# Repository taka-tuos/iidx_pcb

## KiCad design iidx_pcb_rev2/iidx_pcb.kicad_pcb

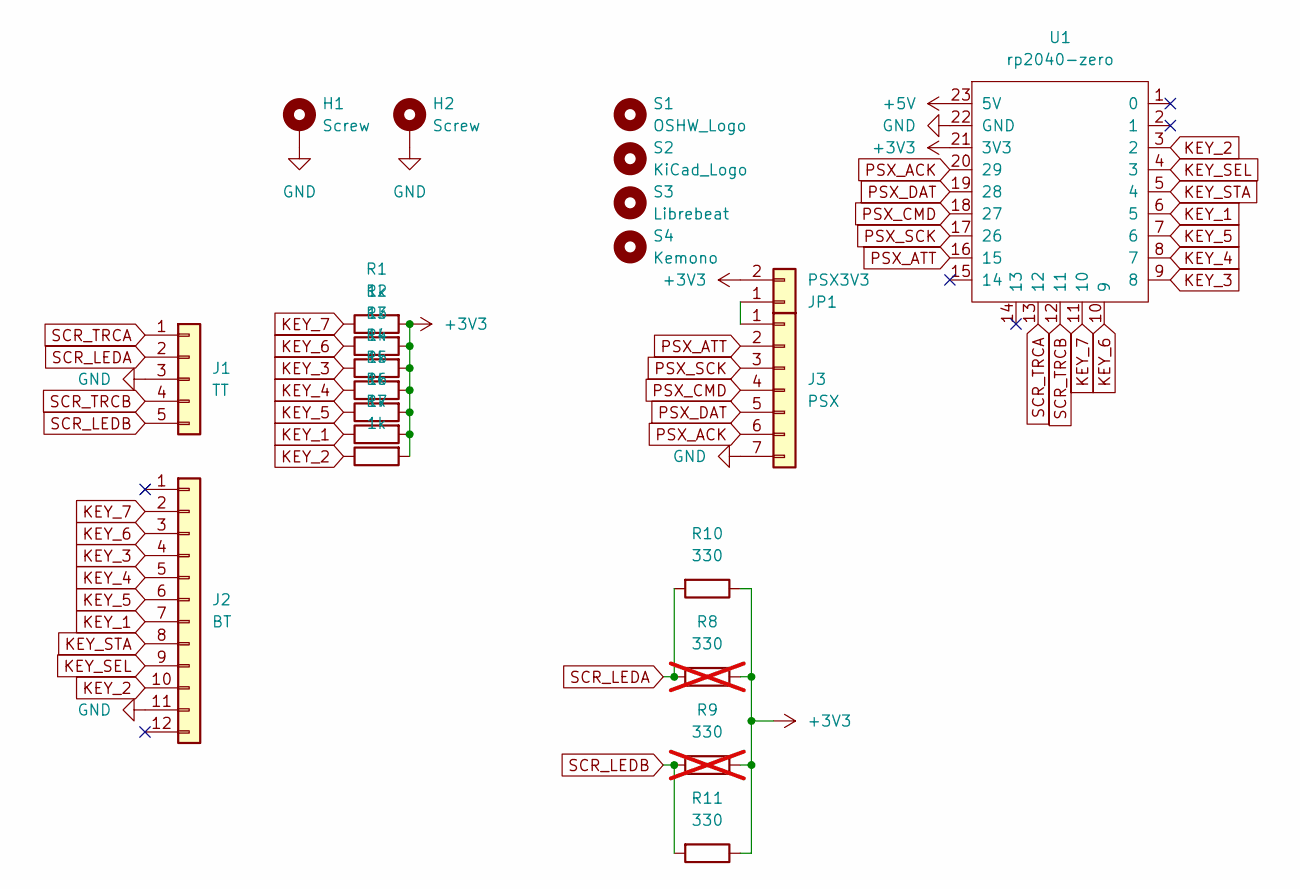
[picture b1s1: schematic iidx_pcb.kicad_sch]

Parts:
H1, H2: Screw; MountingHole_3.2mm_M3_DIN965_Pad
J1: TT; PinSocket_1x05_P2.00mm_Vertical
J2: BT; PinSocket_1x12_P2.00mm_Vertical
J3: PSX; PinSocket_1x07_P2.54mm_Vertical
JP1: PSX3V3; PinHeader_1x02_P2.54mm_Vertical
R1, R2, R3, R4, R5, R6, R7: 1k; R_Axial_DIN0204_L3.6mm_D1.6mm_P5.08mm_Horizontal
R8, R9: 330; R_Axial_DIN0204_L3.6mm_D1.6mm_P5.08mm_Horizontal; not fitted
R10, R11: 330; R_0805_2012Metric_Pad1.20x1.40mm_HandSolder
S1: OSHW_Logo; OSHW-Logo2_9.8x8mm_SilkScreen
S2: KiCad_Logo; KiCad-Logo2_6mm_SilkScreen
S3: Librebeat; Project_Librebeat_Logo
S4: Kemono; Kemono_Symbol
U1: rp2040-zero; rp2040-zero-tht

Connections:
+3V3: JP1.2, R1.2, R2.2, R3.2, R4.2, R5.2, R6.2, R7.2, R8.1, R9.1, R10.1, R11.1, U1.21 (3V3)
+5V: U1.23 (5V)
GND: H1.1, H2.1, J1.3, J2.11, J3.7, U1.22 (GND)
KEY_1: J2.7, R6.1, U1.6 (5)
KEY_2: J2.10, R7.1, U1.3 (2)
KEY_3: J2.4, R3.1, U1.9 (8)
KEY_4: J2.5, R4.1, U1.8 (7)
KEY_5: J2.6, R5.1, U1.7 (6)
KEY_6: J2.3, R2.1, U1.10 (9)
KEY_7: J2.2, R1.1, U1.11 (10)
KEY_SEL: J2.9, U1.4 (3)
KEY_STA: J2.8, U1.5 (4)
unnamed: J3.1, JP1.1
PSX_ACK: J3.6, U1.20 (29)
PSX_ATT: J3.2, U1.16 (15)
PSX_CMD: J3.4, U1.18 (27)
PSX_DAT: J3.5, U1.19 (28)
PSX_SCK: J3.3, U1.17 (26)
SCR_LEDA: J1.2, R8.2, R10.2
SCR_LEDB: J1.5, R9.2, R11.2
SCR_TRCA: J1.1, U1.13 (12)
SCR_TRCB: J1.4, U1.12 (11)

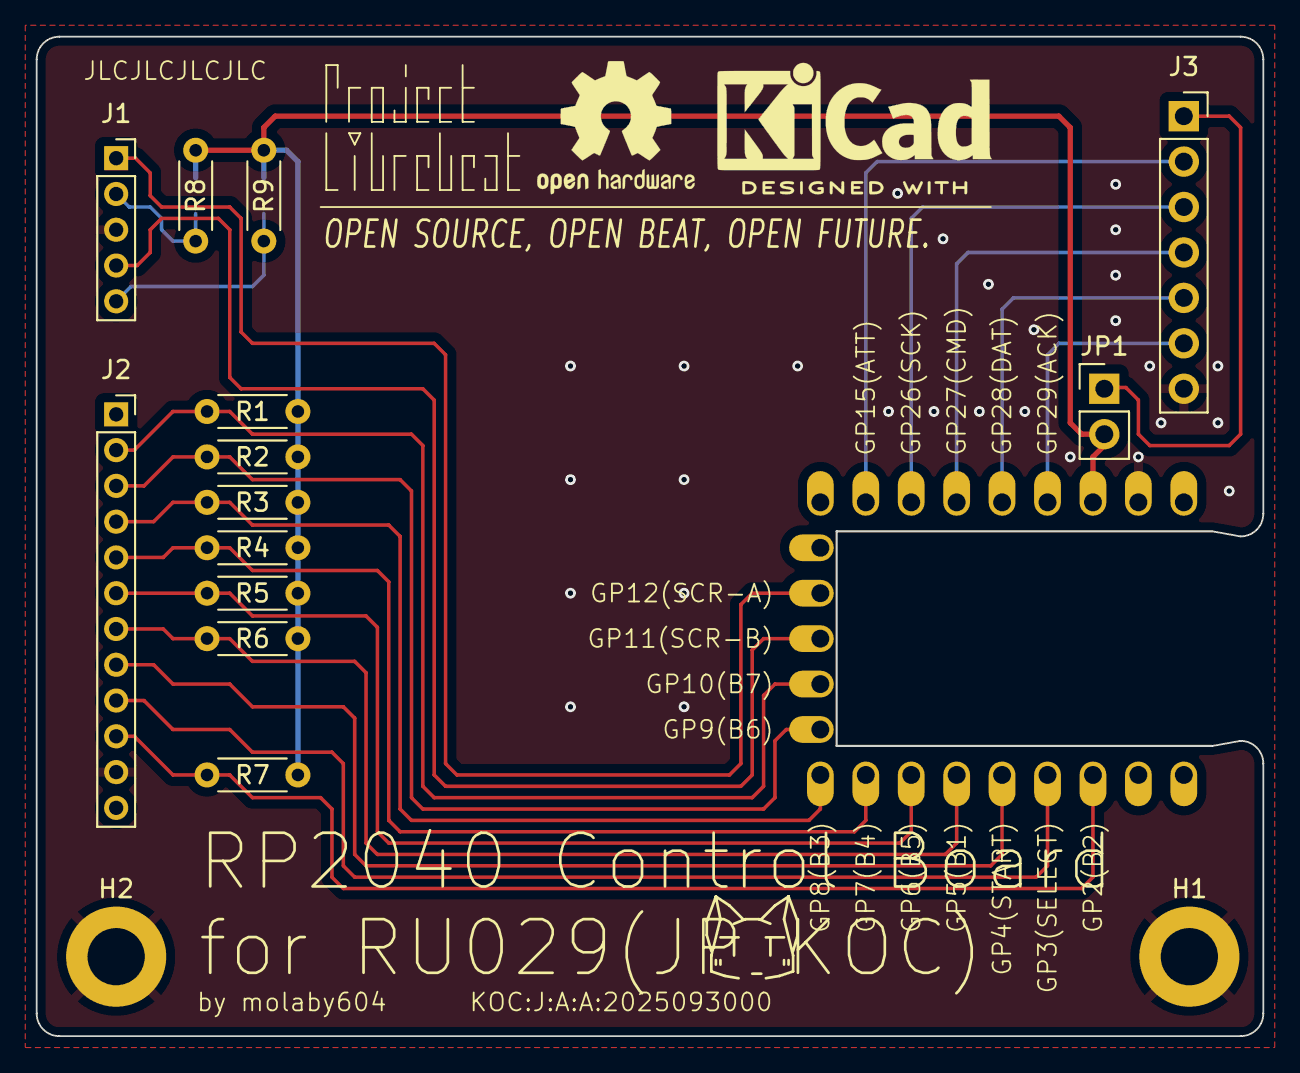
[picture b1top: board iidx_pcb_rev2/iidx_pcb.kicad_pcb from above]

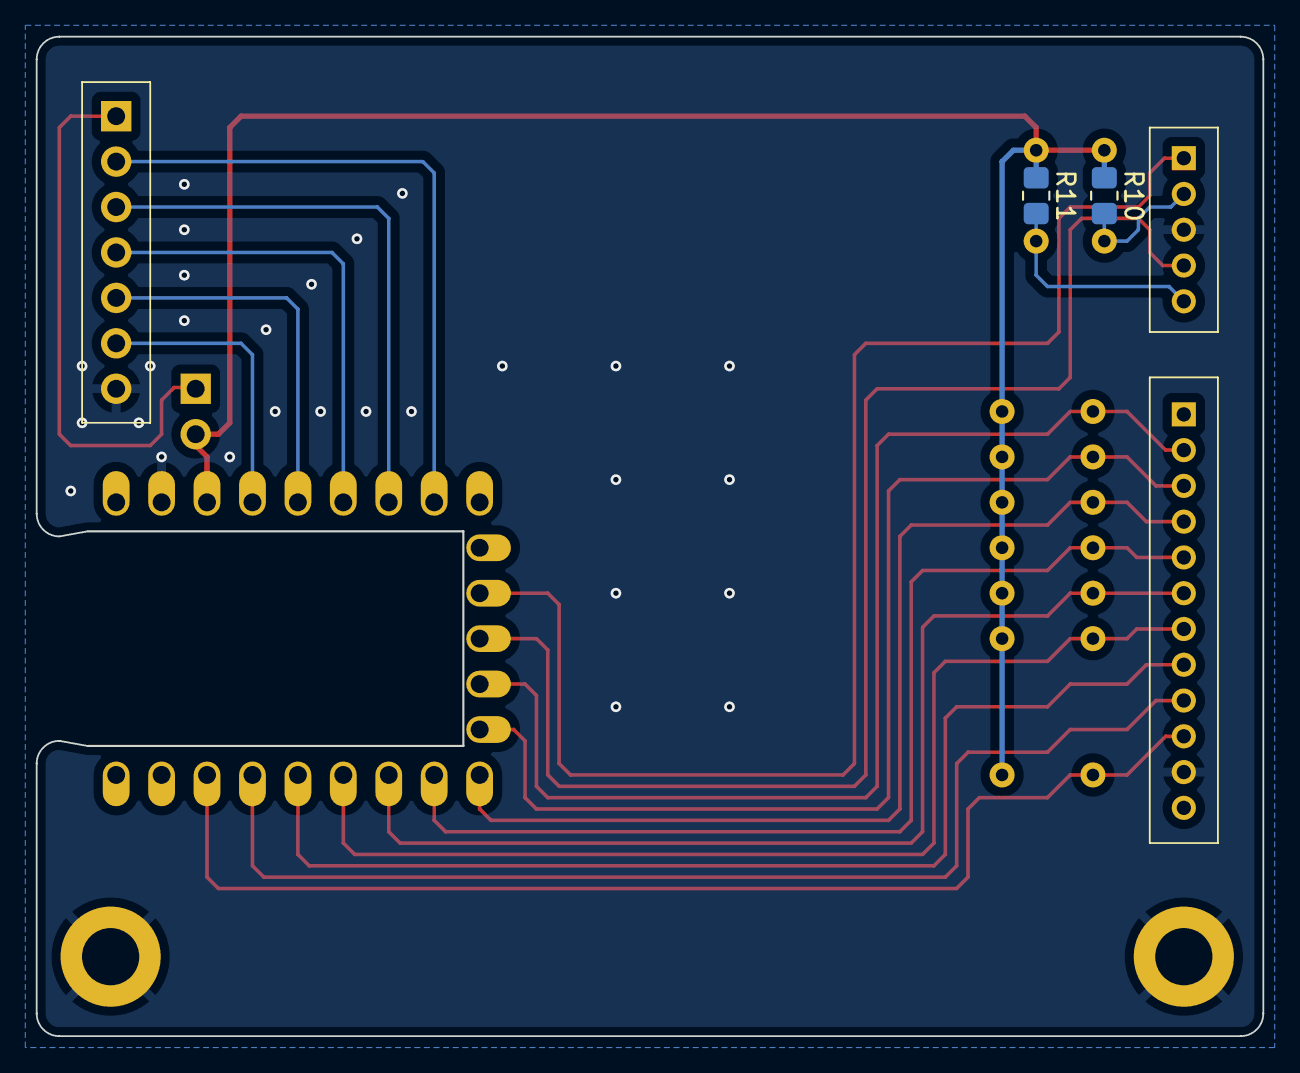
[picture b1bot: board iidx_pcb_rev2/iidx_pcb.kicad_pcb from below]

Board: 2 copper layers, 68.6 x 55.9 mm, 22 parts (2 on the bottom side), 21 nets.

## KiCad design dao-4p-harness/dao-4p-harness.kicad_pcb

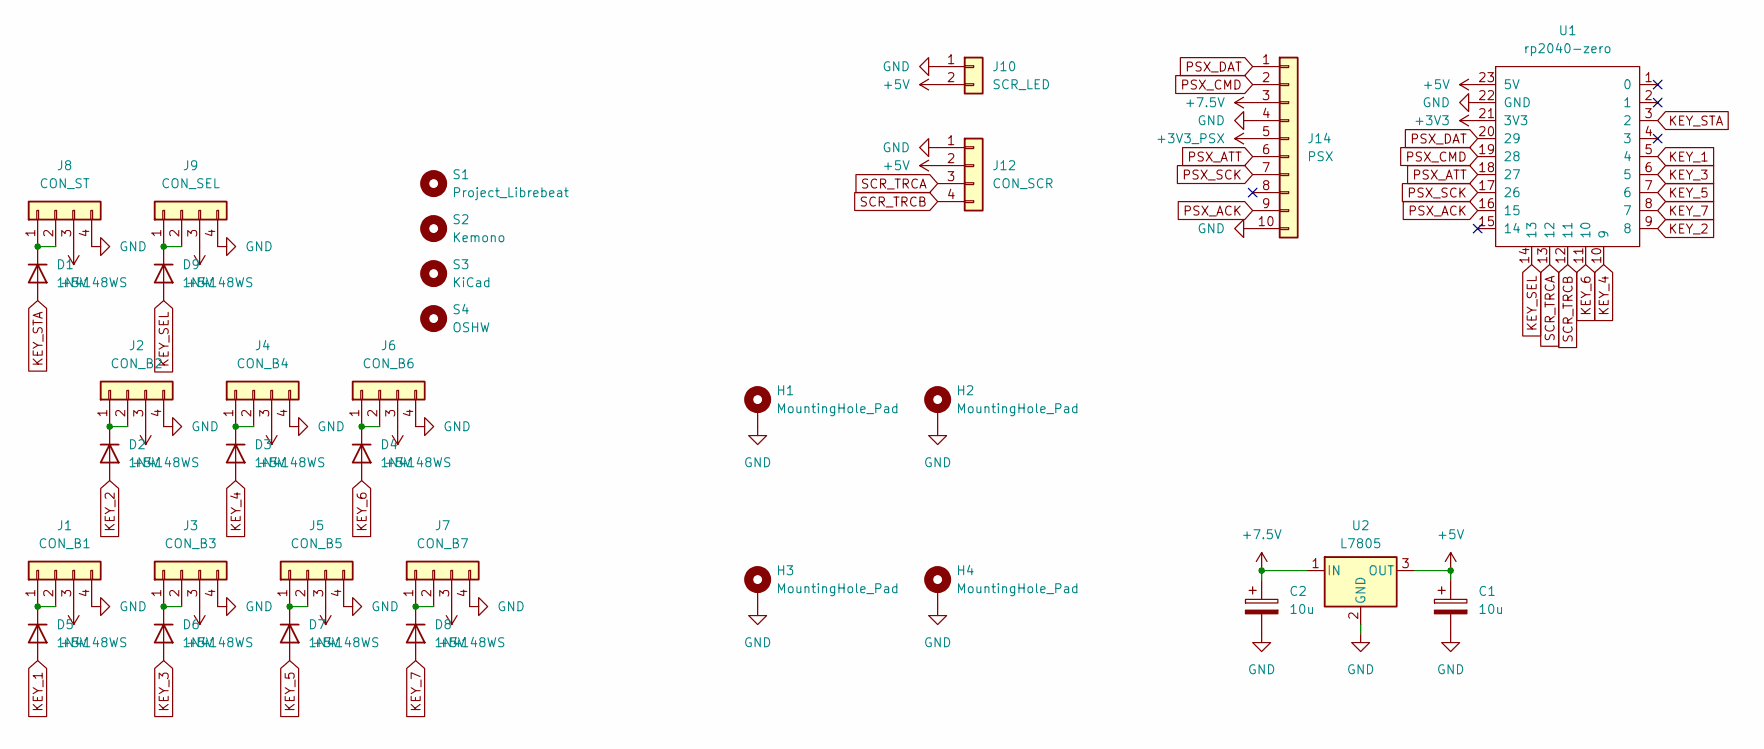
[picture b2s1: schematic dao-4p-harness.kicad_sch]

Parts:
C1, C2: 10u; CP_Radial_D4.0mm_P1.50mm
D1, D2, D3, D4, D5, D6, D7, D8, D9: 1N4148WS; D_SOD-323
H1, H2, H3, H4: MountingHole_Pad; MountingHole_4.3mm_M4_DIN965_Pad
J1: CON_B1; JST_XH_B4B-XH-A_1x04_P2.50mm_Vertical
J2: CON_B2; JST_XH_B4B-XH-A_1x04_P2.50mm_Vertical
J3: CON_B3; JST_XH_B4B-XH-A_1x04_P2.50mm_Vertical
J4: CON_B4; JST_XH_B4B-XH-A_1x04_P2.50mm_Vertical
J5: CON_B5; JST_XH_B4B-XH-A_1x04_P2.50mm_Vertical
J6: CON_B6; JST_XH_B4B-XH-A_1x04_P2.50mm_Vertical
J7: CON_B7; JST_XH_B4B-XH-A_1x04_P2.50mm_Vertical
J8: CON_ST; JST_XH_B4B-XH-A_1x04_P2.50mm_Vertical
J9: CON_SEL; JST_XH_B4B-XH-A_1x04_P2.50mm_Vertical
J10: SCR_LED; JST_XH_B2B-XH-A_1x02_P2.50mm_Vertical
J12: CON_SCR; JST_XH_B4B-XH-A_1x04_P2.50mm_Vertical
J14: PSX; PSX_Male_Vertical
S1: Project_Librebeat; Project_Librebeat_Logo
S2: Kemono; Kemono_Symbol
S3: KiCad; KiCad-Logo2_5mm_SilkScreen
S4: OSHW; OSHW-Logo_7.5x8mm_SilkScreen
U1: rp2040-zero; rp2040-zero-tht
U2: L7805; TO-220-3_Vertical

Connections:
+3V3: U1.21 (3V3)
+3V3_PSX: J14.5
+5V: C1.1, J1.3, J2.3, J3.3, J4.3, J5.3, J6.3, J7.3, J8.3, J9.3, J10.2, J12.2, U1.23 (5V), U2.3 (OUT)
+7.5V: C2.1, J14.3, U2.1 (IN)
GND: C1.2, C2.2, H1.1, H2.1, H3.1, H4.1, J1.4, J2.4, J3.4, J4.4, J5.4, J6.4, J7.4, J8.4, J9.4, J10.1, J12.1, J14.4, J14.10, U1.22 (GND), U2.2 (GND)
KEY_1: D5.2 (A), U1.5 (4)
KEY_2: D2.2 (A), U1.9 (8)
KEY_3: D6.2 (A), U1.6 (5)
KEY_4: D3.2 (A), U1.10 (9)
KEY_5: D7.2 (A), U1.7 (6)
KEY_6: D4.2 (A), U1.11 (10)
KEY_7: D8.2 (A), U1.8 (7)
KEY_SEL: D9.2 (A), U1.14 (13)
KEY_STA: D1.2 (A), U1.3 (2)
unnamed: D1.1 (K), J8.1, J8.2
unnamed: D2.1 (K), J2.1, J2.2
unnamed: D3.1 (K), J4.1, J4.2
unnamed: D4.1 (K), J6.1, J6.2
unnamed: D5.1 (K), J1.1, J1.2
unnamed: D6.1 (K), J3.1, J3.2
unnamed: D7.1 (K), J5.1, J5.2
unnamed: D8.1 (K), J7.1, J7.2
unnamed: D9.1 (K), J9.1, J9.2
PSX_ACK: J14.9, U1.16 (15)
PSX_ATT: J14.6, U1.18 (27)
PSX_CMD: J14.2, U1.19 (28)
PSX_DAT: J14.1, U1.20 (29)
PSX_SCK: J14.7, U1.17 (26)
SCR_TRCA: J12.3, U1.13 (12)
SCR_TRCB: J12.4, U1.12 (11)

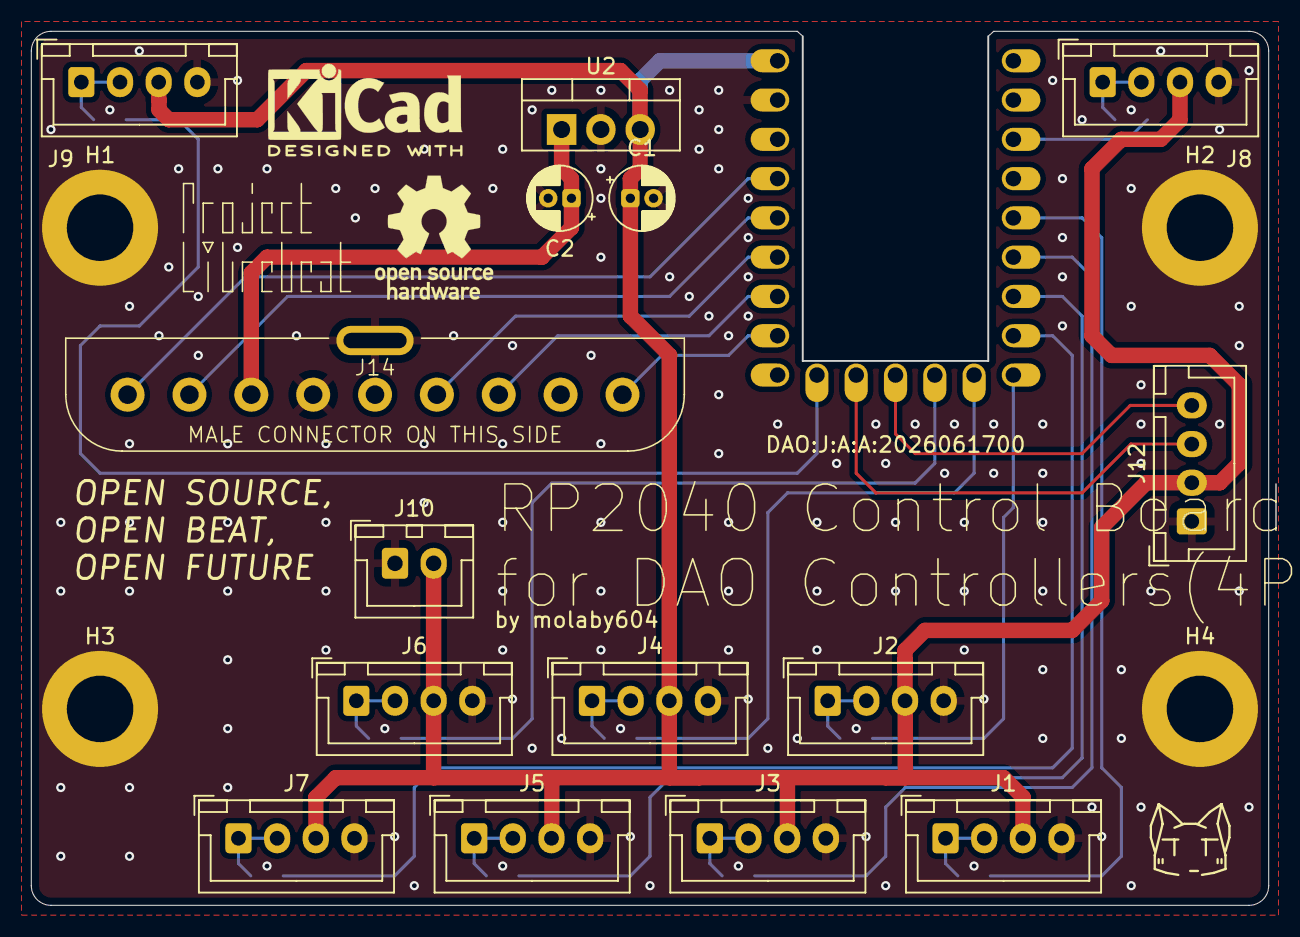
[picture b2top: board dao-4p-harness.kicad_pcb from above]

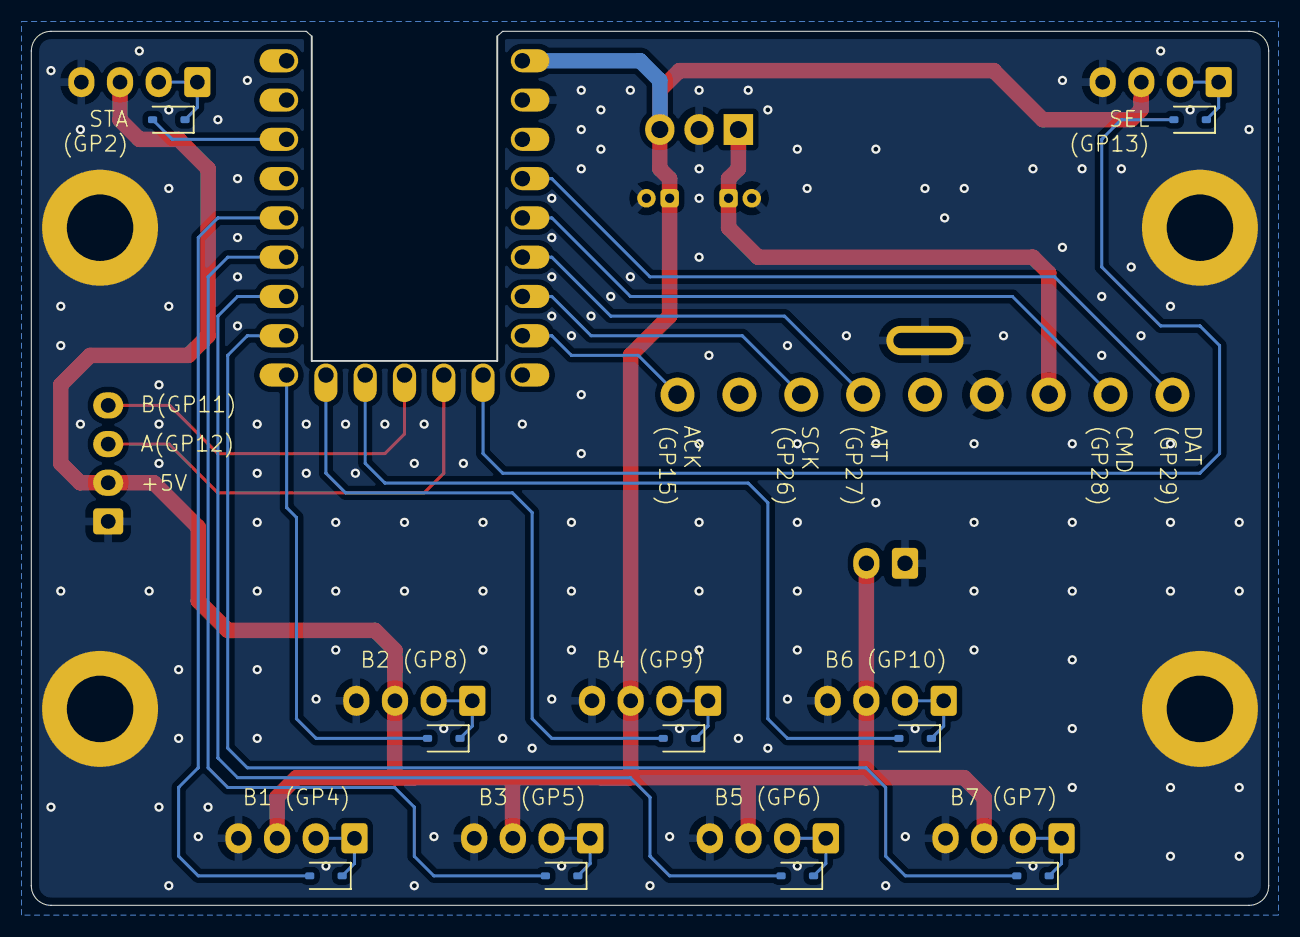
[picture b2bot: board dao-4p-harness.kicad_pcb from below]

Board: 2 copper layers, 80.0 x 56.5 mm, 33 parts (9 on the bottom side), 28 nets.

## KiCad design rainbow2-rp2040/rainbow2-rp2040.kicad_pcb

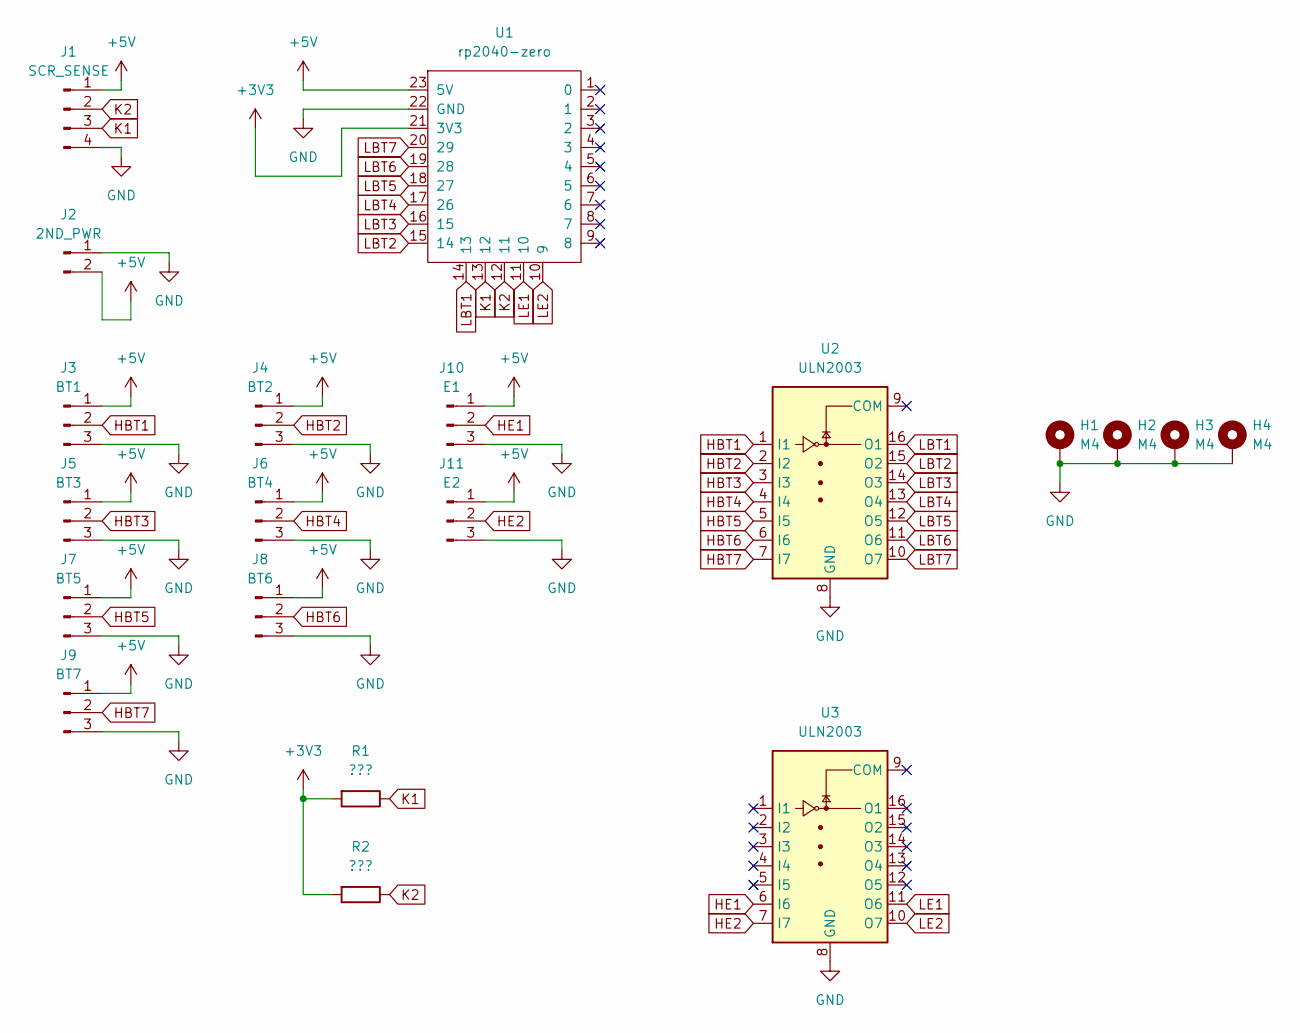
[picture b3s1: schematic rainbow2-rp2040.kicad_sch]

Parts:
H1, H2, H3, H4: M4; MountingHole_4.3mm_M4_DIN965_Pad
J1: SCR_SENSE; JST_XH_B4B-XH-A_1x04_P2.50mm_Vertical
J2: 2ND_PWR; JST_XH_B2B-XH-A_1x02_P2.50mm_Vertical
J3: BT1; JST_XH_B3B-XH-A_1x03_P2.50mm_Vertical
J4: BT2; JST_XH_B3B-XH-A_1x03_P2.50mm_Vertical
J5: BT3; JST_XH_B3B-XH-A_1x03_P2.50mm_Vertical
J6: BT4; JST_XH_B3B-XH-A_1x03_P2.50mm_Vertical
J7: BT5; JST_XH_B3B-XH-A_1x03_P2.50mm_Vertical
J8: BT6; JST_XH_B3B-XH-A_1x03_P2.50mm_Vertical
J9: BT7; JST_XH_B3B-XH-A_1x03_P2.50mm_Vertical
J10: E1; JST_XH_B3B-XH-A_1x03_P2.50mm_Vertical
J11: E2; JST_XH_B3B-XH-A_1x03_P2.50mm_Vertical
R1, R2: ???; R_Axial_DIN0207_L6.3mm_D2.5mm_P10.16mm_Horizontal
U1: rp2040-zero; rp2040-zero-smd
U2, U3: ULN2003; DIP-16_W7.62mm_Socket

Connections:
+3V3: R1.2, R2.2, U1.21 (3V3)
+5V: J1.1, J2.2, J3.1, J4.1, J5.1, J6.1, J7.1, J8.1, J9.1, J10.1, J11.1, U1.23 (5V)
GND: H1.1, H2.1, H3.1, H4.1, J1.4, J2.1, J3.3, J4.3, J5.3, J6.3, J7.3, J8.3, J9.3, J10.3, J11.3, U1.22 (GND), U2.8 (GND), U3.8 (GND)
HBT1: J3.2, U2.1 (I1)
HBT2: J4.2, U2.2 (I2)
HBT3: J5.2, U2.3 (I3)
HBT4: J6.2, U2.4 (I4)
HBT5: J7.2, U2.5 (I5)
HBT6: J8.2, U2.6 (I6)
HBT7: J9.2, U2.7 (I7)
HE1: J10.2, U3.6 (I6)
HE2: J11.2, U3.7 (I7)
K1: J1.3, R1.1, U1.13 (12)
K2: J1.2, R2.1, U1.12 (11)
LBT1: U1.14 (13), U2.16 (O1)
LBT2: U1.15 (14), U2.15 (O2)
LBT3: U1.16 (15), U2.14 (O3)
LBT4: U1.17 (26), U2.13 (O4)
LBT5: U1.18 (27), U2.12 (O5)
LBT6: U1.19 (28), U2.11 (O6)
LBT7: U1.20 (29), U2.10 (O7)
LE1: U1.11 (10), U3.11 (O6)
LE2: U1.10 (9), U3.10 (O7)

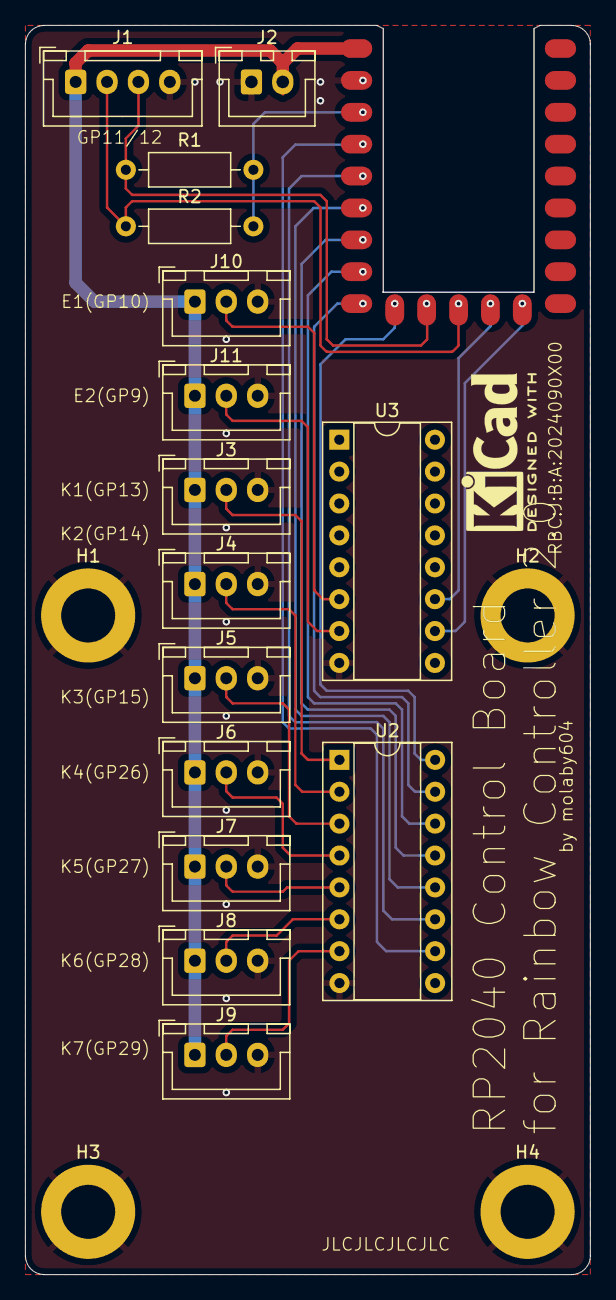
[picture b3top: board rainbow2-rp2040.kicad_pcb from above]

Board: 2 copper layers, 45.0 x 99.5 mm, 20 parts (0 on the bottom side), 23 nets.

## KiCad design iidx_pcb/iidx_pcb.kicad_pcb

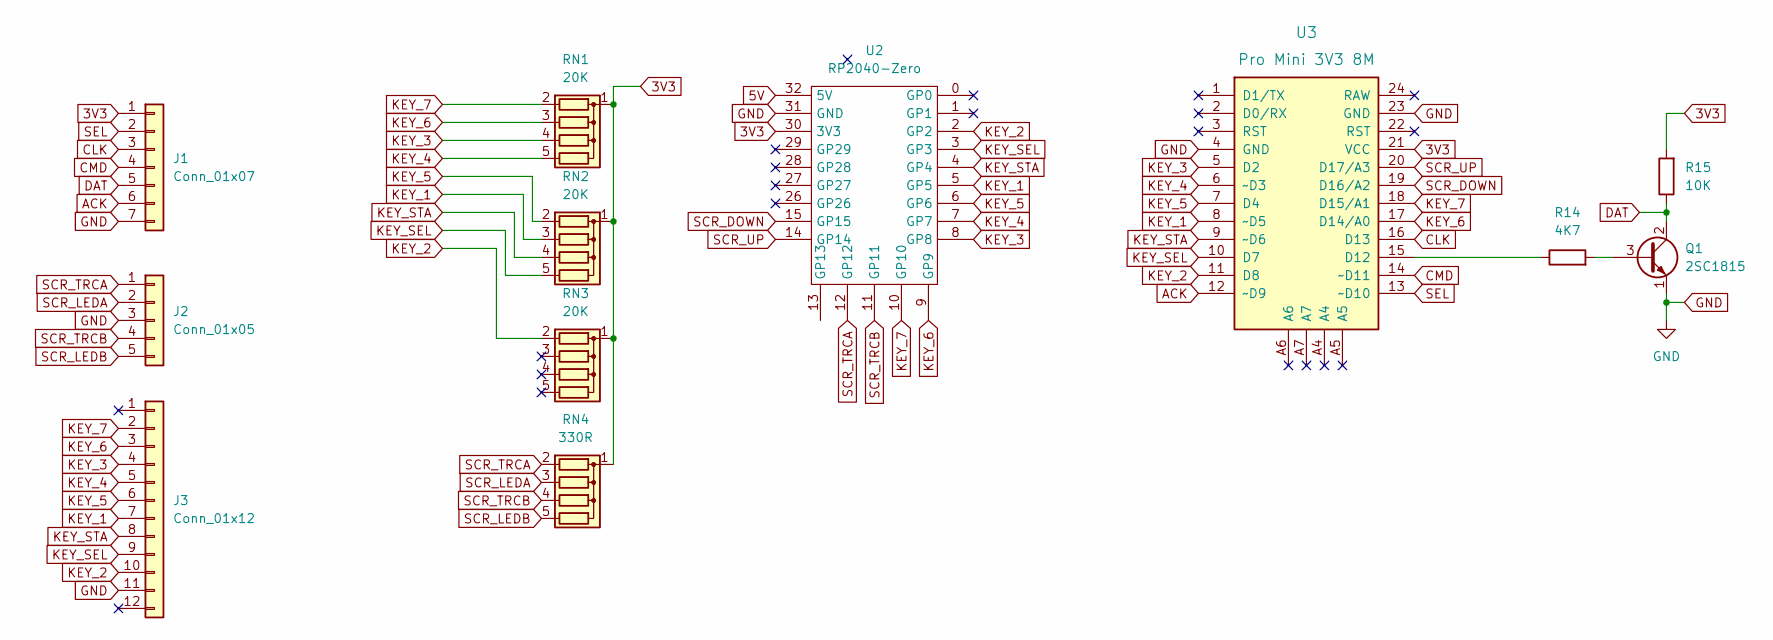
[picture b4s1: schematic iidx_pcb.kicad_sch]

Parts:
J1: Conn_01x07; PinSocket_1x07_P2.54mm_Vertical
J2: Conn_01x05; PinSocket_1x05_P2.00mm_Vertical
J3: Conn_01x12; PinSocket_1x12_P2.00mm_Vertical
Q1: 2SC1815; TO-92L_Inline_Wide
R14: 4K7; R_Axial_DIN0207_L6.3mm_D2.5mm_P10.16mm_Horizontal
R15: 10K; R_Axial_DIN0207_L6.3mm_D2.5mm_P10.16mm_Horizontal
RN1, RN2, RN3: 20K; R_Array_SIP5
RN4: 330R; R_Array_SIP5
U2: RP2040-Zero
U3: Pro Mini 3V3 8M; Arduino_Pro_Mini

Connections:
3V3: J1.1, R15.2, RN1.1 (common), RN2.1 (common), RN3.1 (common), RN4.1 (common), U2.30 (3V3), U3.21 (VCC)
5V: U2.32 (5V)
ACK: J1.6, U3.12 (~D9)
CLK: J1.3, U3.16 (D13)
CMD: J1.4, U3.14 (~D11)
DAT: J1.5, Q1.2 (C), R15.1
GND: J1.7, J2.3, J3.11, Q1.1 (E), U2.31 (GND), U3.4 (GND), U3.23 (GND)
KEY_1: J3.7, RN2.3 (R2), U2.5 (GP5), U3.8 (~D5)
KEY_2: J3.10, RN3.2 (R1), U2.2 (GP2), U3.11 (D8)
KEY_3: J3.4, RN1.4 (R3), U2.8 (GP8), U3.5 (D2)
KEY_4: J3.5, RN1.5 (R4), U2.7 (GP7), U3.6 (~D3)
KEY_5: J3.6, RN2.2 (R1), U2.6 (GP6), U3.7 (D4)
KEY_6: J3.3, RN1.3 (R2), U2.9 (GP9), U3.17 (D14/A0)
KEY_7: J3.2, RN1.2 (R1), U2.10 (GP10), U3.18 (D15/A1)
KEY_SEL: J3.9, RN2.5 (R4), U2.3 (GP3), U3.10 (D7)
KEY_STA: J3.8, RN2.4 (R3), U2.4 (GP4), U3.9 (~D6)
unnamed: Q1.3 (B), R14.2
unnamed: R14.1, U3.15 (D12)
SCR_DOWN: U2.15 (GP15), U3.19 (D16/A2)
SCR_LEDA: J2.2, RN4.3 (R2)
SCR_LEDB: J2.5, RN4.5 (R4)
SCR_TRCA: J2.1, RN4.2 (R1), U2.12 (GP12)
SCR_TRCB: J2.4, RN4.4 (R3), U2.11 (GP11)
SCR_UP: U2.14 (GP14), U3.20 (D17/A3)
SEL: J1.2, U3.13 (~D10)

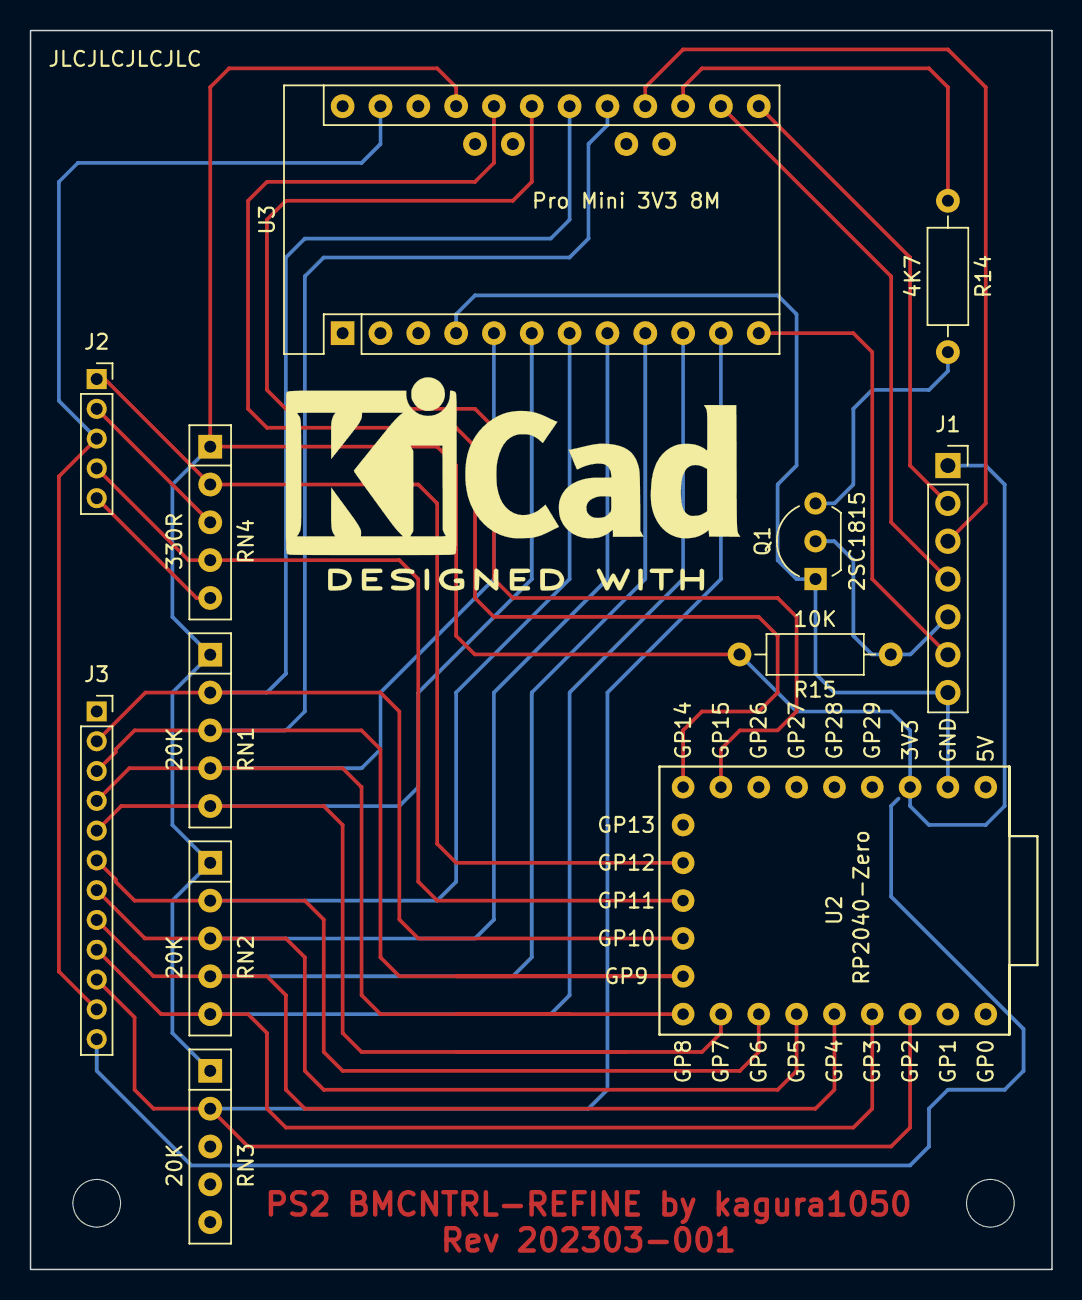
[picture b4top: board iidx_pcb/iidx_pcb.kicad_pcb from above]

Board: 2 copper layers, 68.6 x 83.2 mm, 14 parts (0 on the bottom side), 24 nets.

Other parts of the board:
H1, H2: MountingHole_3.2mm_M3

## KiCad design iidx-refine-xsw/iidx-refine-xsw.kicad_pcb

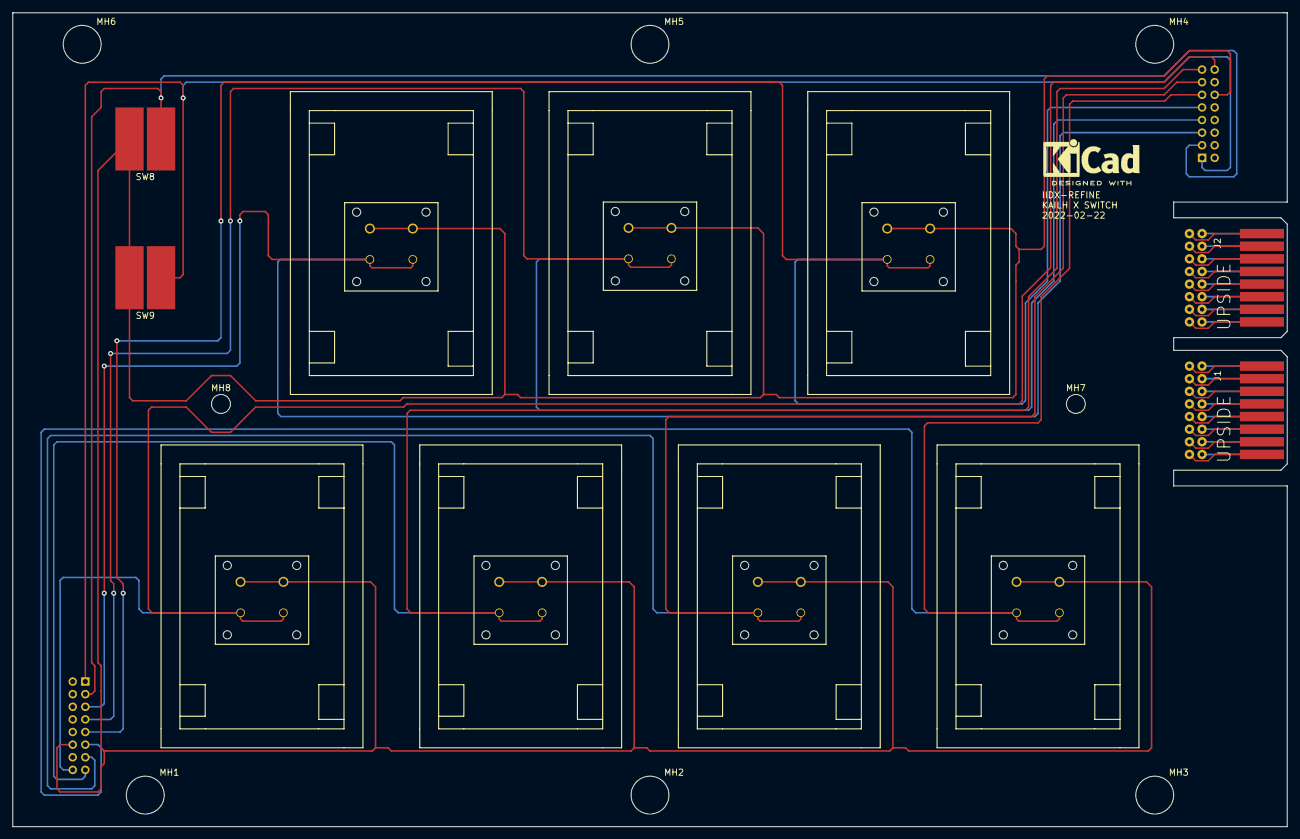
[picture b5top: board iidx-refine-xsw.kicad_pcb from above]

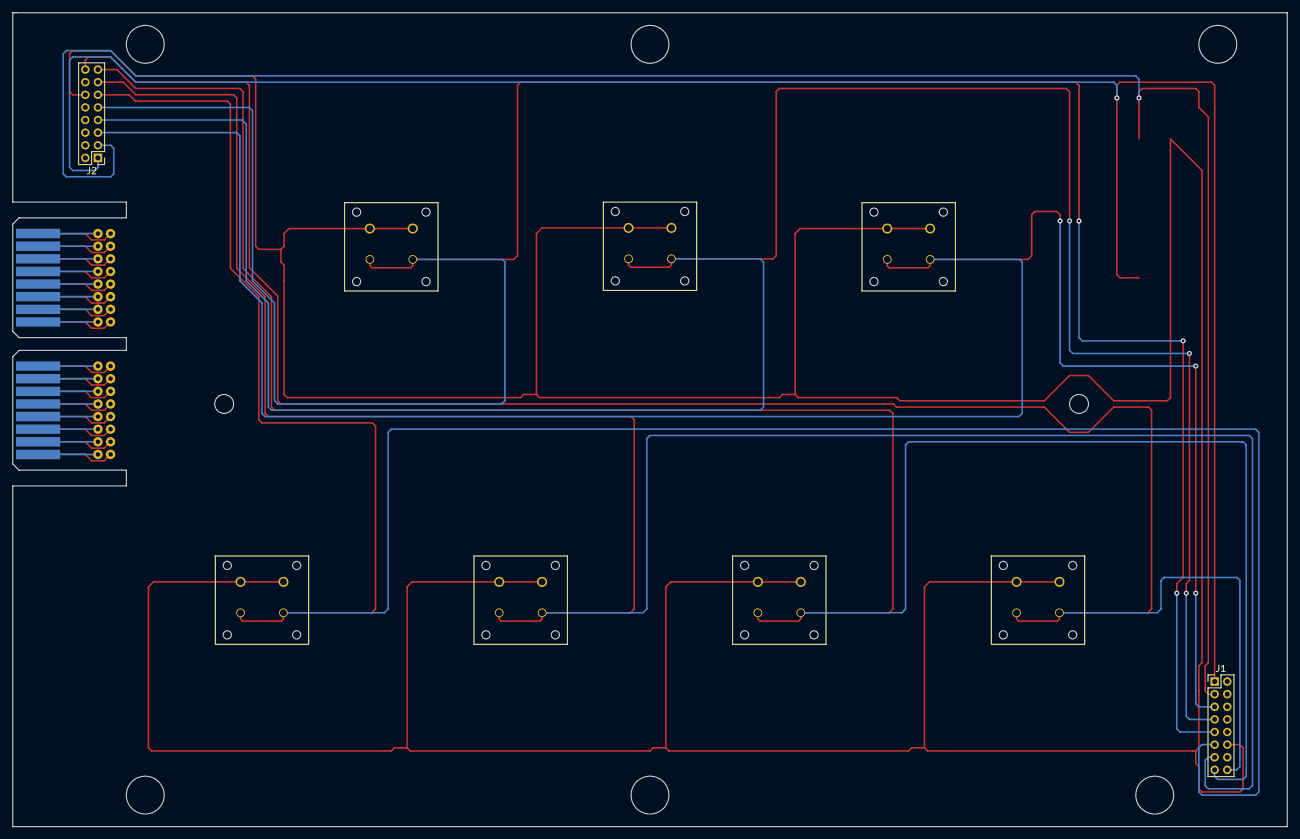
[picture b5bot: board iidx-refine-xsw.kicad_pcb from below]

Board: 2 copper layers, 202.0 x 129.0 mm, 21 parts (2 on the bottom side), 10 nets.

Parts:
J1, J2: Con_IIDX
J1#2, J2#2: Conn_01x16_Female; PinHeader_2x08_P2.00mm_Vertical
MH1, MH2, MH3, MH4, MH5, MH6: Hole-6mm
MH7, MH8: Hole-3mm
SW1, SW2, SW3, SW4, SW5, SW6, SW7: SW_SPST; Kailh-PG1425-X-Switch-reversible
SW8, SW9: SW_SPST; Rubber_Switch

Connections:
GND: J1#2.12, J2#2.12, SW1.1 (A), SW2.1 (A), SW3.1 (A), SW4.1 (A), SW5.1 (A), SW6.1 (A), SW7.1 (A), SW8.1 (A), SW9.1 (A)
unnamed: J1#2.1, J2#2.1, SW9.2 (B)
unnamed: J1#2.3, J2#2.3, SW8.2 (B)
unnamed: J1#2.5, J2#2.5, SW2.2 (B)
unnamed: J1#2.7, J2#2.7, SW4.2 (B)
unnamed: J1#2.9, J2#2.9, SW6.2 (B)
unnamed: J1#2.11, J2#2.11, SW7.2 (B)
unnamed: J1#2.13, J2#2.13, SW5.2 (B)
unnamed: J1#2.15, J2#2.15, SW3.2 (B)
unnamed: J1#2.16, J2#2.16, SW1.2 (B)

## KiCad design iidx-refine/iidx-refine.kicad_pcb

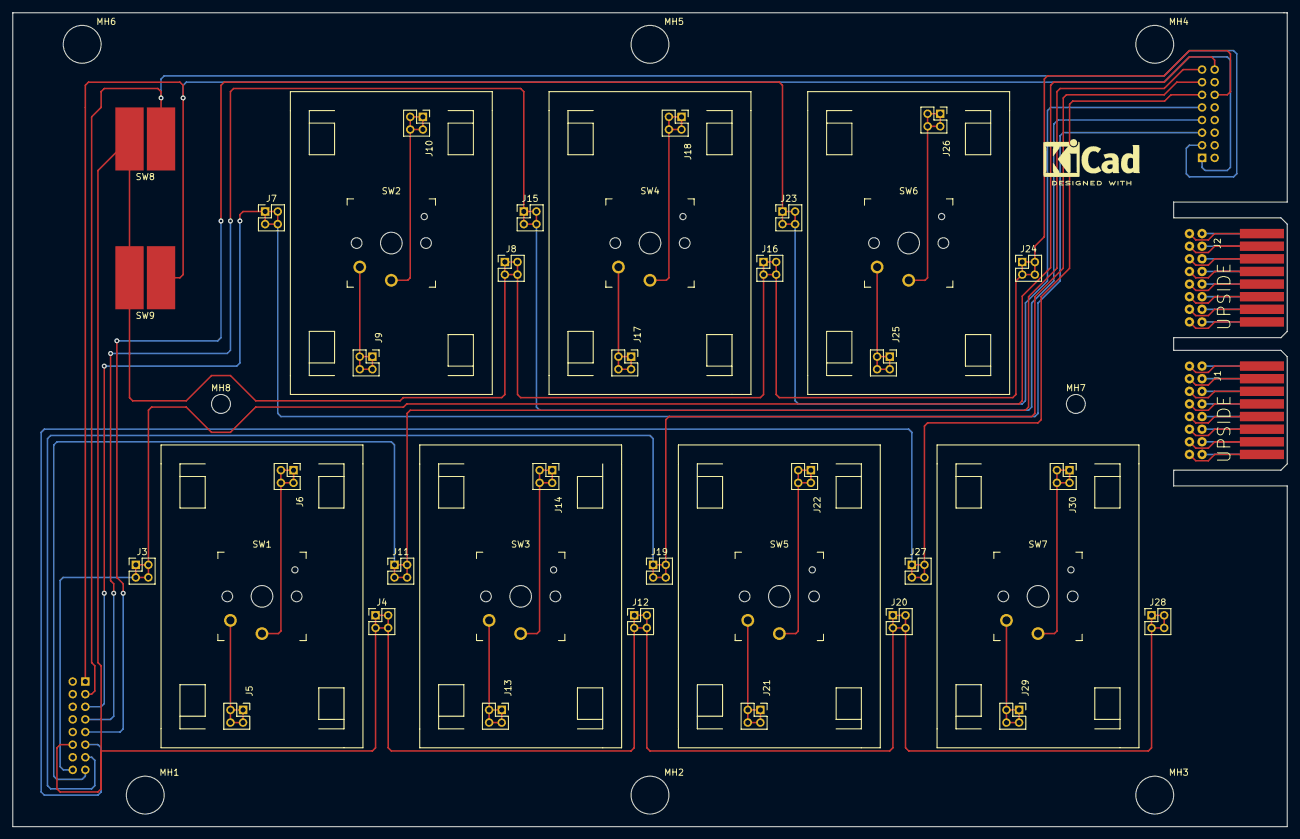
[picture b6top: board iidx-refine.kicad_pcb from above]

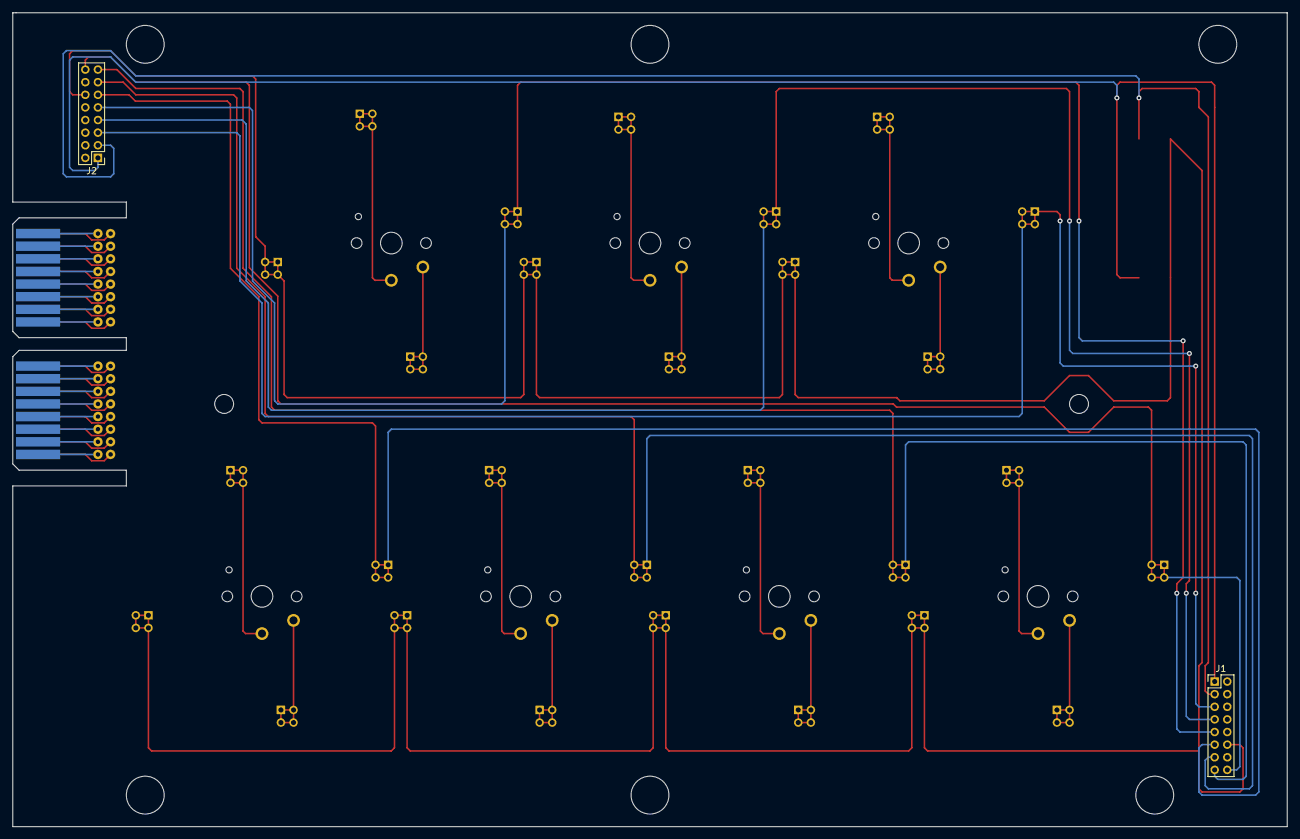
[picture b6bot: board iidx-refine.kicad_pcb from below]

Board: 2 copper layers, 202.0 x 129.0 mm, 49 parts (2 on the bottom side), 24 nets.

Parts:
J1, J2: Con_IIDX
J1#2, J2#2: Conn_01x16_Female; PinHeader_2x08_P2.00mm_Vertical
J3, J4, J5, J6, J7, J8, J9, J10, J11, J12, J13, J14, J15, J16, J17, J18, J19, J20, J21, J22, J23, J24, J25, J26, J27, J28, J29, J30: Conn_01x04_Female; PinHeader_2x02_P2.00mm_Vertical
MH1, MH2, MH3, MH4, MH5, MH6: Hole-6mm
MH7, MH8: Hole-3mm
SW1, SW2, SW3, SW4, SW5, SW6, SW7: SW_SPST; SW_PG1350
SW8, SW9: SW_SPST; Rubber_Switch

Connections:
GND: J1#2.12, J2#2.12, J4.1, J4.2, J4.3, J4.4, J8.1, J8.2, J8.3, J8.4, J12.1, J12.2, J12.3, J12.4, J16.1, J16.2, J16.3, J16.4, J20.1, J20.2, J20.3, J20.4, J24.1, J24.2, J24.3, J24.4, J28.1, J28.2, J28.3, J28.4, SW8.1 (A), SW9.1 (A)
unnamed: J1#2.1, J2#2.1, SW9.2 (B)
unnamed: J1#2.3, J2#2.3, SW8.2 (B)
unnamed: J1#2.16, J2#2.16, J3.1, J3.2, J3.3, J3.4
unnamed: J1#2.5, J2#2.5, J7.1, J7.2, J7.3, J7.4
unnamed: J1#2.15, J2#2.15, J11.1, J11.2, J11.3, J11.4
unnamed: J1#2.7, J2#2.7, J15.1, J15.2, J15.3, J15.4
unnamed: J1#2.13, J2#2.13, J19.1, J19.2, J19.3, J19.4
unnamed: J1#2.9, J2#2.9, J23.1, J23.2, J23.3, J23.4
unnamed: J1#2.11, J2#2.11, J27.1, J27.2, J27.3, J27.4
unnamed: J6.1, J6.2, J6.3, J6.4, SW1.1 (A)
unnamed: J5.1, J5.2, J5.3, J5.4, SW1.2 (B)
unnamed: J10.1, J10.2, J10.3, J10.4, SW2.1 (A)
unnamed: J9.1, J9.2, J9.3, J9.4, SW2.2 (B)
unnamed: J14.1, J14.2, J14.3, J14.4, SW3.1 (A)
unnamed: J13.1, J13.2, J13.3, J13.4, SW3.2 (B)
unnamed: J18.1, J18.2, J18.3, J18.4, SW4.1 (A)
unnamed: J17.1, J17.2, J17.3, J17.4, SW4.2 (B)
unnamed: J22.1, J22.2, J22.3, J22.4, SW5.1 (A)
unnamed: J21.1, J21.2, J21.3, J21.4, SW5.2 (B)
unnamed: J26.1, J26.2, J26.3, J26.4, SW6.1 (A)
unnamed: J25.1, J25.2, J25.3, J25.4, SW6.2 (B)
unnamed: J30.1, J30.2, J30.3, J30.4, SW7.1 (A)
unnamed: J29.1, J29.2, J29.3, J29.4, SW7.2 (B)
